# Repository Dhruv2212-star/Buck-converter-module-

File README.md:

This is a really simple project made from the data sheets avalable for LM2596  
lets learn what each component does by dividing it into easy and understandable blocks  
1. Block 1 – Input Power Stage
   
| Component                              | Purpose                                               | Role in the Circuit                                                                                                                                         |
| -------------------------------------- | ----------------------------------------------------- | ----------------------------------------------------------------------------------------------------------------------------------------------------------- |
| **J1 – Input Terminal Block**          | Receives the external DC input supply.                | Serves as the entry point of the circuit. Pin 1 provides the **VIN** rail, while Pin 2 provides the **GND** return path for the entire converter.           |
| **C1 – 220 µF Electrolytic Capacitor** | Stores input energy and filters low-frequency ripple. | Supplies the large transient currents demanded by the LM2596 during switching, preventing the input voltage from sagging and improving converter stability. |
| **C2 – 100 nF Ceramic Capacitor**      | Filters high-frequency switching noise.               | Provides a low-impedance path for high-frequency noise that the electrolytic capacitor cannot effectively filter, reducing EMI and input voltage spikes.    |

2. Block 2 – LM2596 Power Stage

| Component                         | Purpose                                 | Role in the Circuit                                                                                                                                                                          |
| --------------------------------- | --------------------------------------- | -------------------------------------------------------------------------------------------------------------------------------------------------------------------------------------------- |
| **U1 – LM2596SX-ADJ/NOPB**        | Performs the DC-DC buck conversion.     | Acts as the controller of the converter by switching the input voltage at approximately 150 kHz. It adjusts the duty cycle using the feedback signal to maintain a regulated output voltage. |
| **D1 – MBR340T3G Schottky Diode** | Provides the freewheeling current path. | When the LM2596 switch turns OFF, the inductor continues supplying current through D1. The Schottky diode minimizes forward voltage drop, improving efficiency.                              |
| **L1 – 33 µH Power Inductor**     | Stores and transfers energy.            | Charges while the LM2596 switch is ON and releases stored energy when the switch turns OFF, converting the switching waveform into a continuous output current.                              |

3. Block 3 – Output Filter

| Component                              | Purpose                                                | Role in the Circuit                                                                                                      |
| -------------------------------------- | ------------------------------------------------------ | ------------------------------------------------------------------------------------------------------------------------ |
| **C3 – 330 µF Electrolytic Capacitor** | Filters low-frequency output ripple and stores energy. | Smooths the output voltage, supplies transient load current, and minimizes voltage fluctuations at the converter output. |
| **C4 – 100 nF Ceramic Capacitor**      | Removes high-frequency noise.                          | Filters high-frequency switching spikes remaining after the inductor, improving output voltage quality and reducing EMI. |

4. Block 4 – Feedback & Voltage Adjustment

| Component                                | Purpose                           | Role in the Circuit                                                                                                                                   |
| ---------------------------------------- | --------------------------------- | ----------------------------------------------------------------------------------------------------------------------------------------------------- |
| **R2 – Upper Feedback Resistor (15 kΩ)** | Samples the output voltage.       | Forms the upper section of the feedback divider, scaling the output voltage before it reaches the feedback network.                                   |
| **RV1 – 5 kΩ Multi-turn Trimmer**        | Allows output voltage adjustment. | Adjusts the divider ratio so the user can vary the output voltage while the LM2596 regulates the FB pin to approximately 1.23 V.                      |
| **R1 – Lower Feedback Resistor (1 kΩ)**  | Completes the feedback divider.   | Connects the FB node to ground, establishing the reference point for the voltage divider and determining the output voltage together with R2 and RV1. |

5. Block 5 – Status Indicator
   
| Component              | Purpose                        | Role in the Circuit                                                                                                                     |
| ---------------------- | ------------------------------ | --------------------------------------------------------------------------------------------------------------------------------------- |
| **R3 – 1 kΩ Resistor** | Limits LED current.            | Protects the LED by limiting the current flowing through it, ensuring reliable operation.                                               |
| **LED1 – Green LED**   | Indicates converter operation. | Illuminates whenever **VOUT** is present, providing a visual indication that the regulator is successfully producing an output voltage. |

6. Block 6 – Output Connector  

| Component                      | Purpose                                   | Role in the Circuit                                                                                                                 |
| ------------------------------ | ----------------------------------------- | ----------------------------------------------------------------------------------------------------------------------------------- |
| **J2 – Output Terminal Block** | Provides connection to the external load. | Delivers the regulated **VOUT** and **GND** to external circuits or devices, serving as the output interface of the buck converter. |

# THAT"S IT!! it's REALLY EASY, BUILD IT UR SELF!!

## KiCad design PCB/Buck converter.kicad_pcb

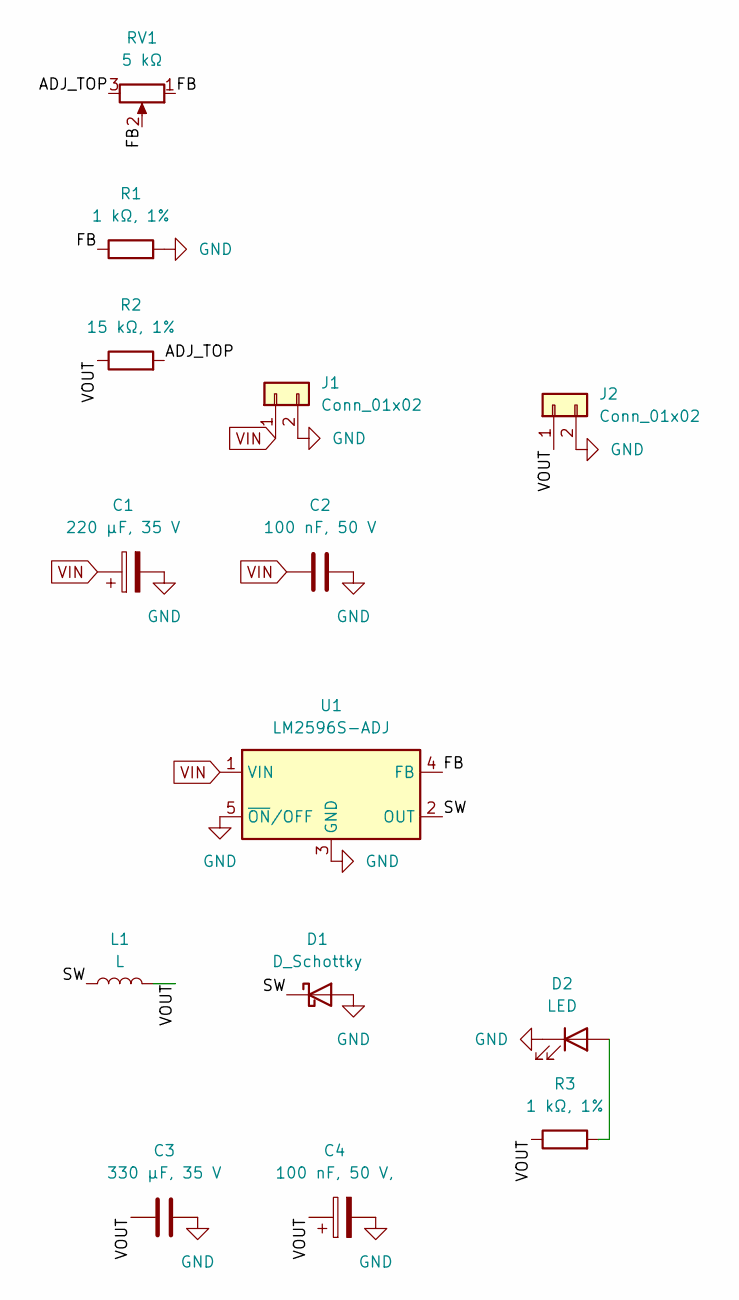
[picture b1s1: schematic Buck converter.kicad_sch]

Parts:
C1: 220 µF, 35 V; CP_Radial_D10.0mm_P5.00mm
C2: 100 nF, 50 V; C_1206_3216Metric
C3: 330 µF, 35 V; CP_Radial_D10.0mm_P5.00mm
C4: 100 nF, 50 V,; C_1206_3216Metric
D1: D_Schottky; TO-277A
D2: LED; LED_1206_3216Metric
J1, J2: Conn_01x02; TerminalBlock_Phoenix_MKDS-1,5-2-5.08_1x02_P5.08mm_Horizont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
L1: L; L_Bourns_SRR1260
R1, R3: 1 kΩ, 1%; R_1206_3216Metric
R2: 15 kΩ, 1%; R_1206_3216Metric
RV1: 5 kΩ; Potentiometer_Bourns_3296W_Vertical
U1: LM2596S-ADJ; TO-263-5_TabPin3

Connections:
/ADJ_TOP: R2.2, RV1.3
/FB: R1.1, RV1.1, RV1.2, U1.4 (FB)
/SW: D1.1 (K), L1.1, U1.2 (OUT)
/VOUT: C3.1, C4.1, J2.1, L1.2, R2.1, R3.1
GND: C1.2, C2.2, C3.2, C4.2, D1.2 (A), D2.1 (K), J1.2, J2.2, R1.2, U1.3 (GND), U1.5 (~ON/OFF)
unnamed: D2.2 (A), R3.2
VIN: C1.1, C2.1, J1.1, U1.1 (VIN)

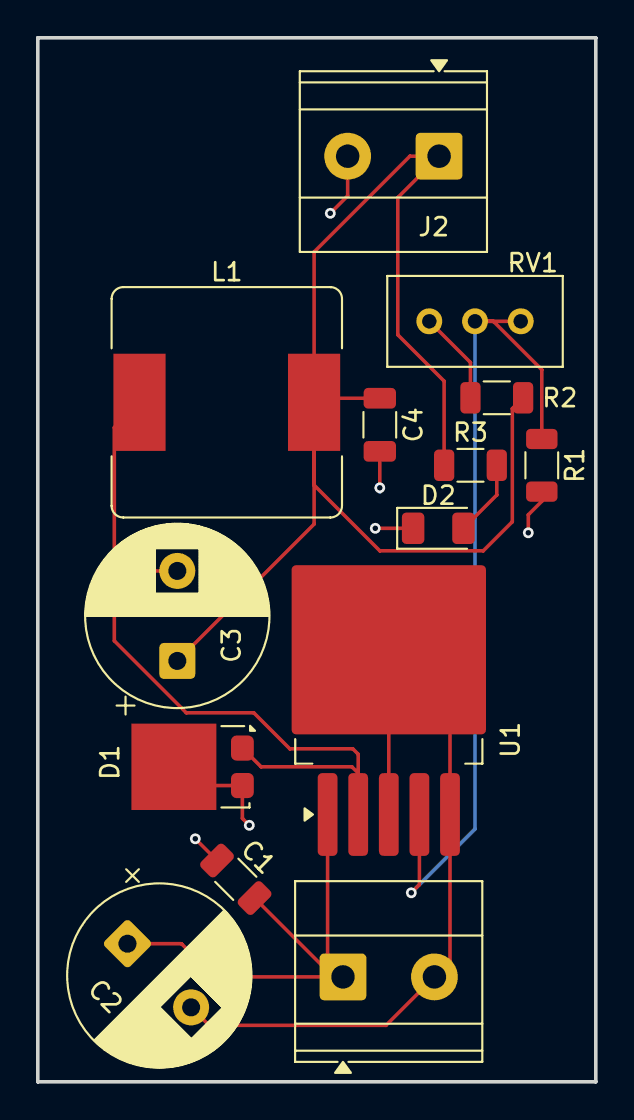
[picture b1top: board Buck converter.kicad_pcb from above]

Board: 2 copper layers, 31.0 x 58.0 mm, 14 parts (0 on the bottom side), 7 nets.
